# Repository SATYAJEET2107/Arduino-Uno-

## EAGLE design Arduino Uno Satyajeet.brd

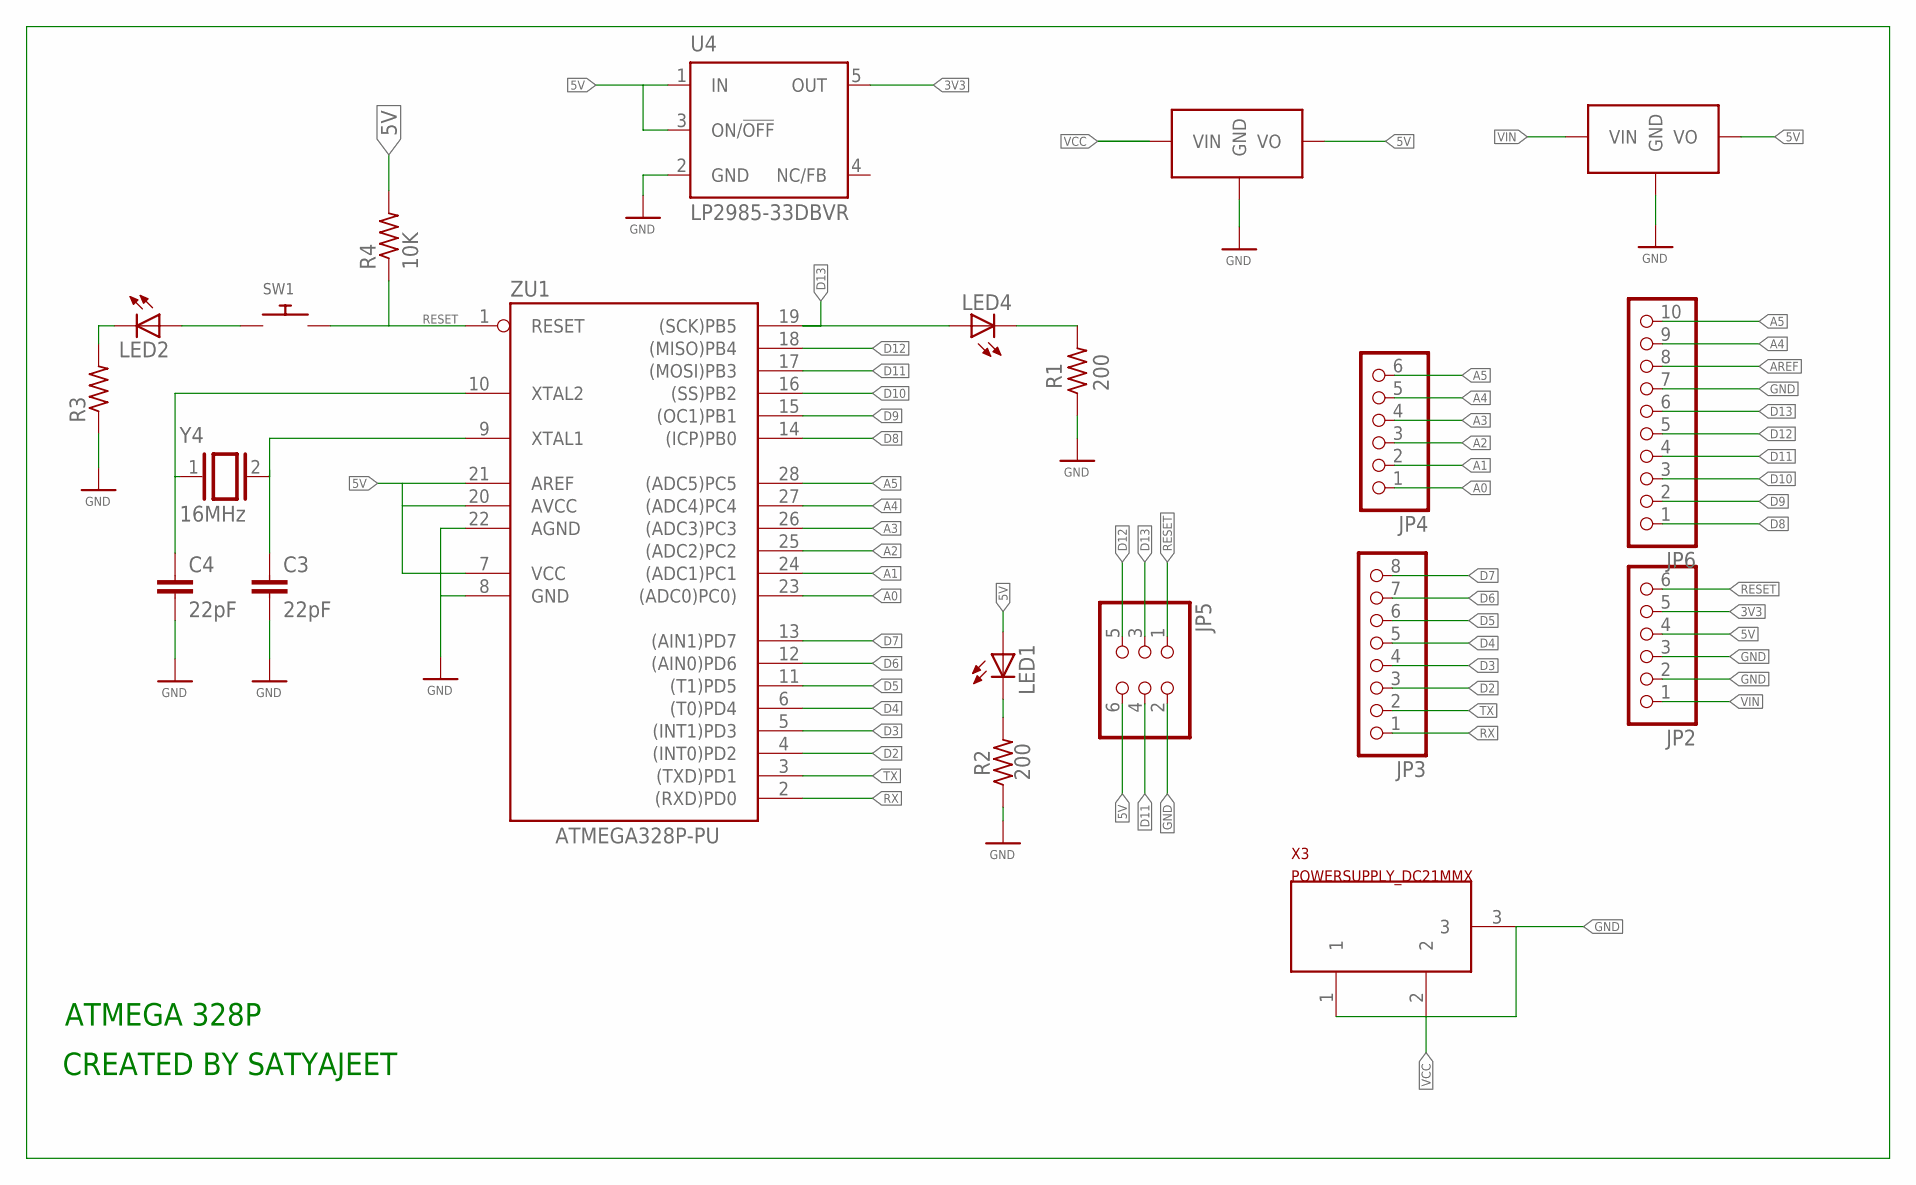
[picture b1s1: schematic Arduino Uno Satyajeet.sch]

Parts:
C3, C4: 22pF; C2.5-2
JP2, JP4: PINHD-1X6; 1X06
JP3: PINHD-1X8; 1X08
JP5: PINHD-2X3; 2X03
JP6: PINHD-1X10; 1X10
LED1, LED2, LED4: LED5MM
R1, R2: 200; 0204/5
R3: R-US_0204/5; 0204/5
R4: 10K; 0204/5
SW1: SWITCH_PUSHBUTTONEVQ-PE; TACT_PANA-EVQ
U4: LP2985-33DBVR; SOT23-DBV
U$1, U$2: AB_7805_FLAT
X3: POWERSUPPLY_DC21MMX; POWERSUPPLY_DC-21MM
Y4: 16MHz; QS
ZU1: ATMEGA328P-PU; DIL28-3

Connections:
3V3: JP2.5, U4.5 (OUT)
5V: JP2.4, JP5.6, LED1.A, R4.2, U4.1 (IN), U$1.3 (VO), U$2.3 (VO), ZU1.21 (AREF)
A0: JP4.1, ZU1.23 ((ADC0)PC0))
A1: JP4.2, ZU1.24 ((ADC1)PC1)
A2: JP4.3, ZU1.25 ((ADC2)PC2)
A3: JP4.4, ZU1.26 ((ADC3)PC3)
A4: JP4.5, JP6.9, ZU1.27 ((ADC4)PC4)
A5: JP4.6, JP6.10, ZU1.28 ((ADC5)PC5)
AREF: JP6.8
D2: JP3.3, ZU1.4 ((INT0)PD2)
D3: JP3.4, ZU1.5 ((INT1)PD3)
D4: JP3.5, ZU1.6 ((T0)PD4)
D5: JP3.6, ZU1.11 ((T1)PD5)
D6: JP3.7, ZU1.12 ((AIN0)PD6)
D7: JP3.8, ZU1.13 ((AIN1)PD7)
D8: JP6.1, ZU1.14 ((ICP)PB0)
D9: JP6.2, ZU1.15 ((OC1)PB1)
D10: JP6.3, ZU1.16 ((SS)PB2)
D11: JP5.4, JP6.4, ZU1.17 ((MOSI)PB3)
D12: JP5.5, JP6.5, ZU1.18 ((MISO)PB4)
D13: JP5.3, JP6.6, LED4.A, ZU1.19 ((SCK)PB5)
GND: C3.2, C4.2, JP2.2, JP2.3, JP5.2, JP6.7, R1.1, R2.1, R3.1, U4.2 (GND), U$1.2 (GND), U$2.2 (GND), X3.1, X3.3, ZU1.22 (AGND)
unnamed: C3.1, Y4.2, ZU1.9 (XTAL1)
unnamed: C4.1, Y4.1, ZU1.10 (XTAL2)
unnamed: LED2.A, SW1.P$1
unnamed: LED2.K (C), R3.2
unnamed: LED4.K (C), R1.2
unnamed: LED1.K (C), R2.2
RESET: JP2.6, JP5.1, SW1.P$2, ZU1.1 (RESET)
RX: JP3.1, ZU1.2 ((RXD)PD0)
TX: JP3.2, ZU1.3 ((TXD)PD1)
VCC: U$1.1 (VIN), X3.2
VIN: JP2.1, U$2.1 (VIN)

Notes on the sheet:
ATMEGA 328P
CREATED BY SATYAJEET

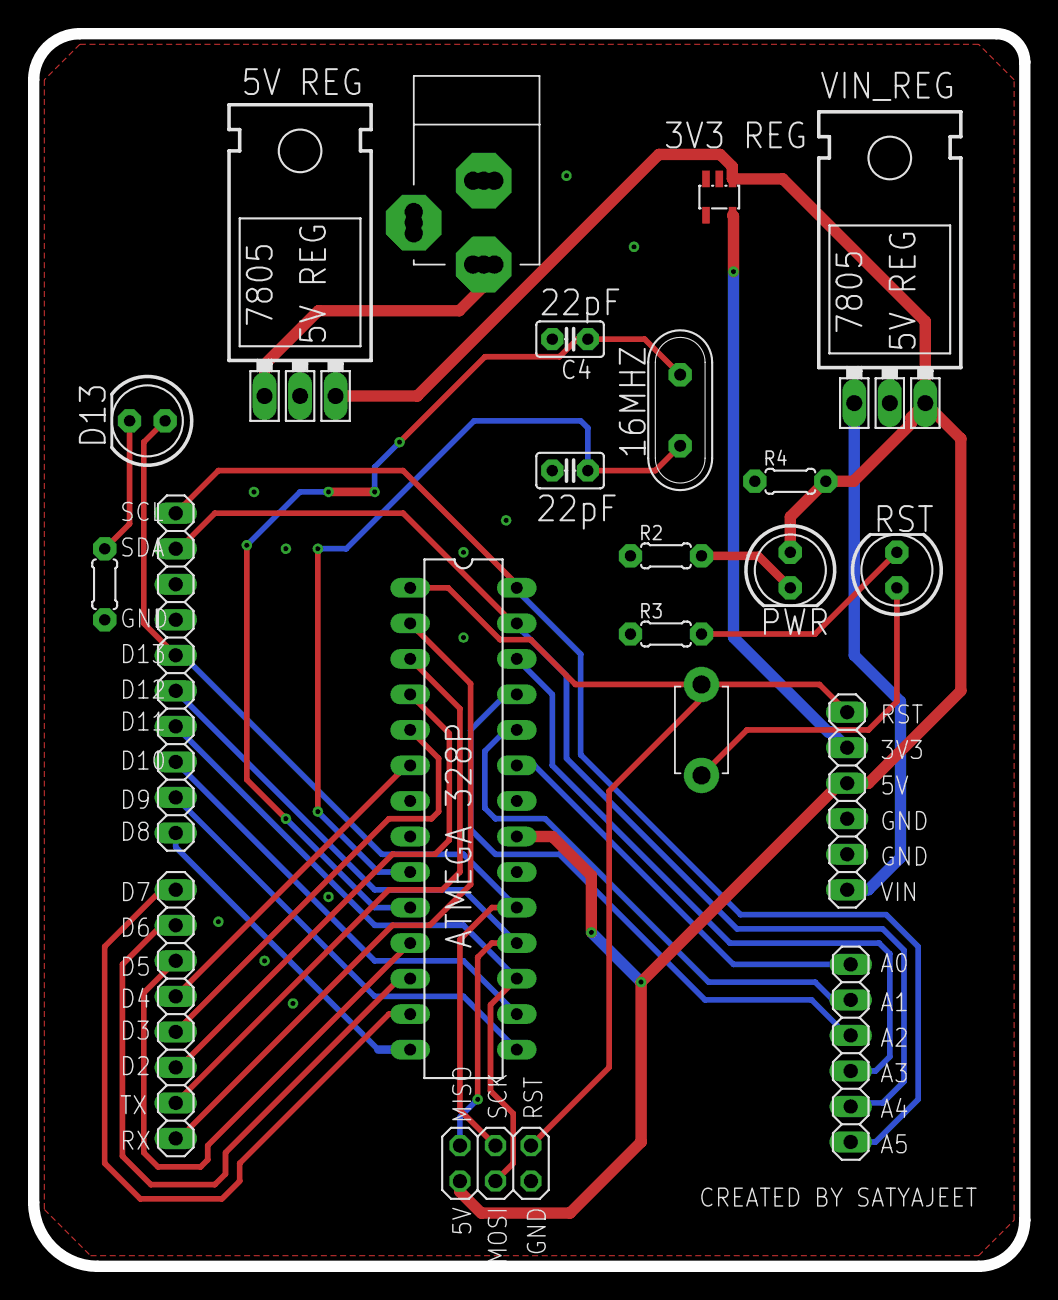
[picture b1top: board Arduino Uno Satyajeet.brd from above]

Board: 2 copper layers, 70.9 x 88.1 mm, 21 parts (0 on the bottom side), 32 nets.
